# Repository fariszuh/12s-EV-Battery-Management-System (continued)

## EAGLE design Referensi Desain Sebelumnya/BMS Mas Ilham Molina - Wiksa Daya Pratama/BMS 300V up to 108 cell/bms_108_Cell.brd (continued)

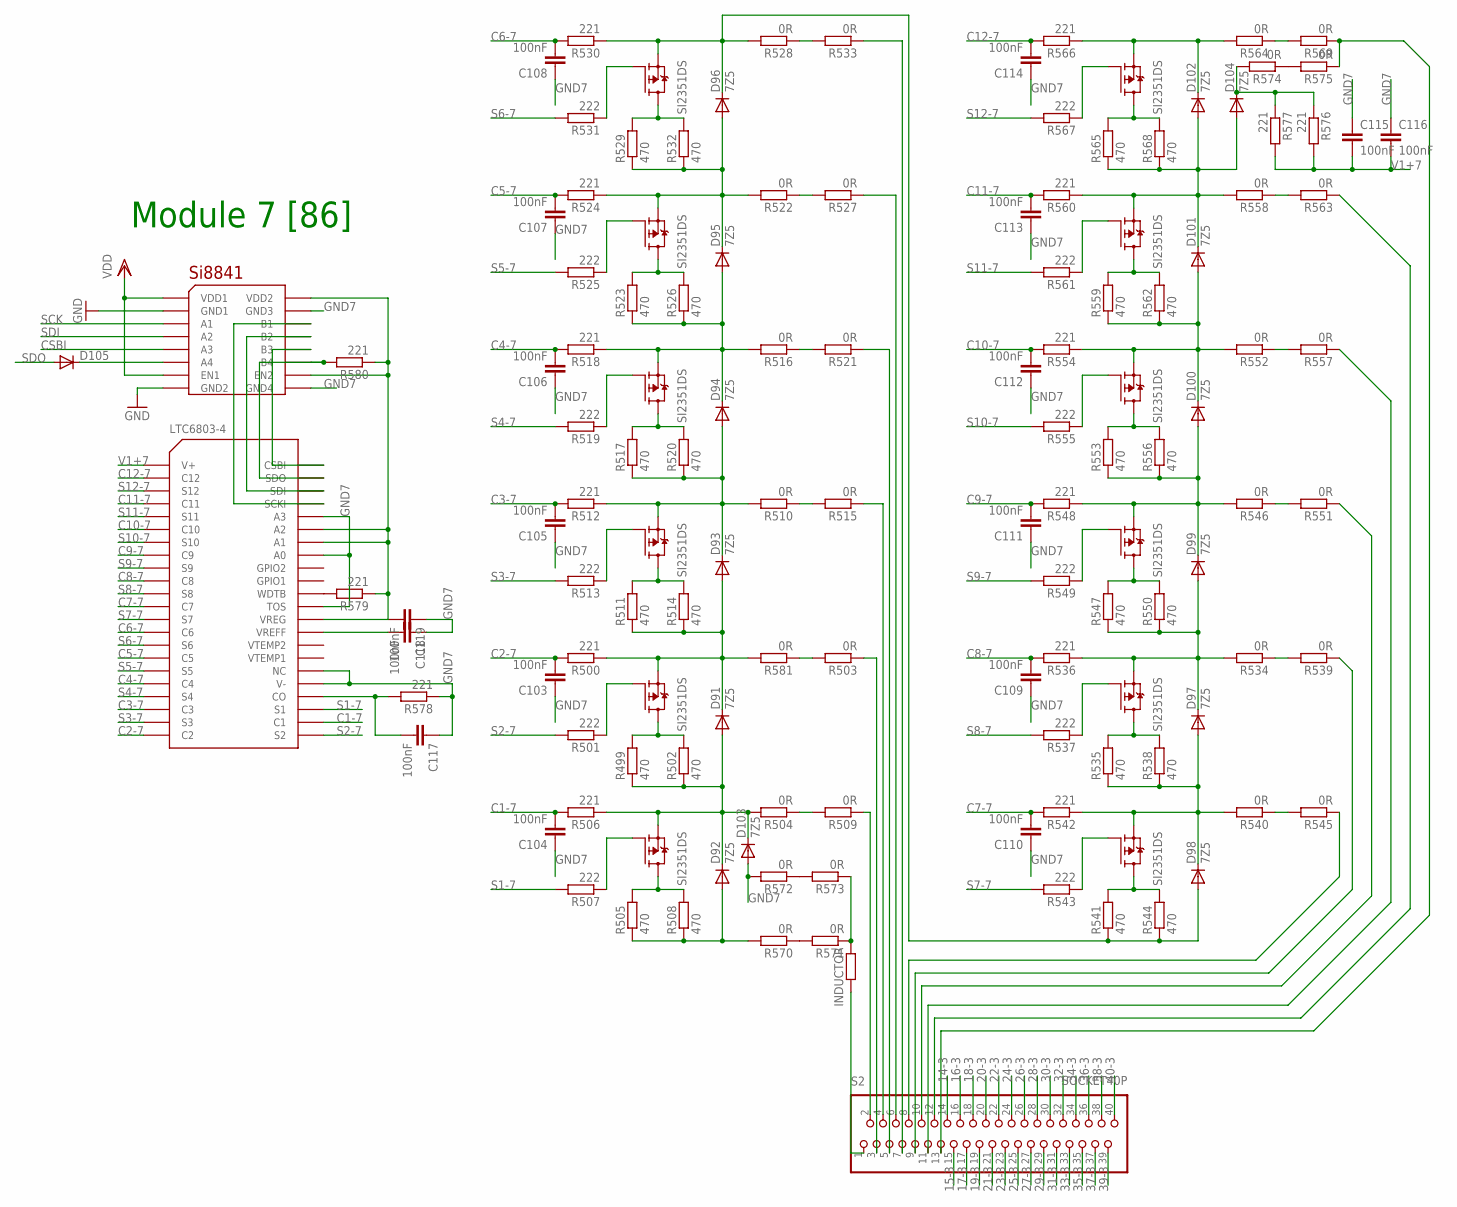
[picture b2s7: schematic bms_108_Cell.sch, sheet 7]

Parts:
C103, C104, C105, C106, C107, C108, C109, C110, C111, C112, C113, C114, C115, C116, C117, C118, C119: 100nF; C0805K
D91, D92, D93, D94, D95, D96, D97, D98, D99, D100, D101, D102, D103, D104: 7Z5; SMB
D105: DIODE-SOD123; SOD123
R499, R502, R505, R508, R511, R514, R517, R520, R523, R526, R529, R532, R535, R538, R541, R544, R547, R550, R553, R556, R559, R562, R565, R568: 470; R6332
R500, R506, R512, R518, R524, R530, R536, R542, R548, R554, R560, R566, R576, R577, R578, R579, R580: 221; R0805
R501, R507, R513, R519, R525, R531, R537, R543, R549, R555, R561, R567: 222; R0805
R503, R504, R509, R510, R515, R516, R521, R522, R527, R528, R533, R534, R539, R540, R545, R546, R551, R552, R557, R558, R563, R564, R569, R570, R571, R572, R573, R574, R575, R581: 0R; M1206
S2: SOCKET40P; 40PIN
U$91: LTC6803-4; SSOP44
U$92: SI8841; SO16
U$93, U$94, U$95, U$96, U$97, U$98, U$99, U$100, U$101, U$102, U$103, U$104: SI2351DS; SOT23
U$105: INDUCTOR; L2012C

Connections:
14-3: S2.14; also elsewhere on the board
15-3: S2.15; also elsewhere on the board
16-3: S2.16; also elsewhere on the board
17-3: S2.17; also elsewhere on the board
18-3: S2.18; also elsewhere on the board
19-3: S2.19; also elsewhere on the board
20-3: S2.20; also elsewhere on the board
21-3: S2.21; also elsewhere on the board
22-3: S2.22; also elsewhere on the board
23-3: S2.23; also elsewhere on the board
24-3: S2.24; also elsewhere on the board
25-3: S2.25; also elsewhere on the board
26-3: S2.26; also elsewhere on the board
27-3: S2.27
28-3: S2.28; also elsewhere on the board
29-3: S2.29; also elsewhere on the board
30-3: S2.30; also elsewhere on the board
31-3: S2.31; also elsewhere on the board
32-3: S2.32; also elsewhere on the board
33-3: S2.33; also elsewhere on the board
34-3: S2.34; also elsewhere on the board
35-3: S2.35; also elsewhere on the board
36-3: S2.36; also elsewhere on the board
37-3: S2.37; also elsewhere on the board
38-3: S2.38; also elsewhere on the board
39-3: S2.39; also elsewhere on the board
40-3: S2.40; also elsewhere on the board
C1-7: C104.2, R506.2, U$91.24 (C1)
C2-7: C103.2, R500.2, U$91.P$22 (C2)
C3-7: C105.2, R512.2, U$91.P$20 (C3)
C4-7: C106.2, R518.2, U$91.P$18 (C4)
C5-7: C107.2, R524.2, U$91.P$16 (C5)
C6-7: C108.2, R530.2, U$91.P$14 (C6)
C7-7: C110.2, R542.2, U$91.P$12 (C7)
C8-7: C109.2, R536.2, U$91.P$10 (C8)
C9-7: C111.2, R548.2, U$91.P$8 (C9)
C10-7: C112.2, R554.2, U$91.P$6 (C10)
C11-7: C113.2, R560.2, U$91.P$4 (C11)
C12-7: C114.2, R566.2, U$91.P$2 (C12)
CSBI: U$92.5 (A3); also elsewhere on the board
GND: U$92.2 (GND1), U$92.8 (GND2); also elsewhere on the board
GND7: C103.1, C104.1, C105.1, C106.1, C107.1, C108.1, C109.1, C110.1, C111.1, C112.1, C113.1, C114.1, C115.1, C116.1, C117.1, C118.1, C119.1, D103.A, R572.2, R578.1, U$91.27 (V-), U$91.28 (NC), U$91.33 (TOS), U$91.37 (A0), U$91.40 (A3), U$92.9 (GND4), U$92.15 (GND3)
unnamed: R501.1, U$93.1 (G)
unnamed: R499.2, R502.2, U$93.3 (D)
unnamed: D91.A, D92.C, D103.C, R499.1, R502.1, R504.2, R506.1, U$94.2 (S)
unnamed: R503.2, R581.1
unnamed: R507.1, U$94.1 (G)
unnamed: R505.2, R508.2, U$94.3 (D)
unnamed: R504.1, R509.2
unnamed: R513.1, U$95.1 (G)
unnamed: R511.2, R514.2, U$95.3 (D)
unnamed: D91.C, D93.A, R500.1, R511.1, R514.1, R581.2, U$93.2 (S)
unnamed: R510.1, R515.2
unnamed: R519.1, U$96.1 (G)
unnamed: R517.2, R520.2, U$96.3 (D)
unnamed: D93.C, D94.A, R510.2, R512.1, R517.1, R520.1, U$95.2 (S)
unnamed: R516.1, R521.2
unnamed: R525.1, U$97.1 (G)
unnamed: R523.2, R526.2, U$97.3 (D)
unnamed: D94.C, D95.A, R516.2, R518.1, R523.1, R526.1, U$96.2 (S)
unnamed: R522.1, R527.2
unnamed: R531.1, U$98.1 (G)
unnamed: R529.2, R532.2, U$98.3 (D)
unnamed: D95.C, D96.A, R522.2, R524.1, R529.1, R532.1, U$97.2 (S)
unnamed: R528.1, R533.2
unnamed: R537.1, U$99.1 (G)
unnamed: R535.2, R538.2, U$99.3 (D)
unnamed: D97.A, D98.C, R535.1, R538.1, R540.2, R542.1, U$100.2 (S)
unnamed: R534.1, R539.2
unnamed: R543.1, U$100.1 (G)
unnamed: R541.2, R544.2, U$100.3 (D)
unnamed: D96.C, D98.A, R528.2, R530.1, R541.1, R544.1, U$98.2 (S)
unnamed: R540.1, R545.2
unnamed: R549.1, U$101.1 (G)
unnamed: R547.2, R550.2, U$101.3 (D)
unnamed: D97.C, D99.A, R534.2, R536.1, R547.1, R550.1, U$99.2 (S)
unnamed: R546.1, R551.2
unnamed: R555.1, U$102.1 (G)
unnamed: R553.2, R556.2, U$102.3 (D)
unnamed: D99.C, D100.A, R546.2, R548.1, R553.1, R556.1, U$101.2 (S)
unnamed: R552.1, R557.2
unnamed: R561.1, U$103.1 (G)
unnamed: R559.2, R562.2, U$103.3 (D)
unnamed: D100.C, D101.A, R552.2, R554.1, R559.1, R562.1, U$102.2 (S)
unnamed: R558.1, R563.2
unnamed: D102.C, R564.2, R566.1, U$104.2 (S)
unnamed: R567.1, U$104.1 (G)
unnamed: R565.2, R568.2, U$104.3 (D)
unnamed: D101.C, D102.A, D104.A, R558.2, R560.1, R565.1, R568.1, U$103.2 (S)
unnamed: R564.1, R569.2
unnamed: R570.1, R571.2
unnamed: R571.1, R573.1, U$105.1
unnamed: D92.A, R505.1, R508.1, R570.2
unnamed: R572.1, R573.2
unnamed: R574.1, R575.2
unnamed: D104.C, R574.2, R576.1, R577.1
unnamed: R569.1, R575.1, S2.13
unnamed: C117.2, R578.2, U$91.26 (CO)
unnamed: C118.2, U$91.31 (VREFF)
unnamed: C119.2, R579.1, R580.1, U$91.32 (VREG), U$91.38 (A1), U$91.39 (A2), U$92.10 (EN2), U$92.16 (VDD2)
unnamed: R579.2, U$91.34 (WDTB)
unnamed: R580.2, U$91.43 (SDO), U$92.11 (B4)
unnamed: U$91.44 (CSBI), U$92.12 (B3)
unnamed: U$91.42 (SDI), U$92.13 (B2)
unnamed: U$91.41 (SCKI), U$92.14 (B1)
unnamed: S2.1, U$105.2
unnamed: R509.1, S2.2
unnamed: R503.1, S2.3
unnamed: R515.1, S2.4
unnamed: R521.1, S2.5
unnamed: R527.1, S2.6
unnamed: R533.1, S2.7
unnamed: R545.1, S2.8
unnamed: R539.1, S2.9
unnamed: R551.1, S2.10
unnamed: R557.1, S2.11
unnamed: R563.1, S2.12
unnamed: D105.C, U$92.6 (A4)
S1-7: R507.2, U$91.25 (S1)
S2-7: R501.2, U$91.23 (S2)
S3-7: R513.2, U$91.P$21 (S3)
S4-7: R519.2, U$91.P$19 (S4)
S5-7: R525.2, U$91.P$17 (S5)
S6-7: R531.2, U$91.P$15 (S6)
S7-7: R543.2, U$91.P$13 (S7)
S8-7: R537.2, U$91.P$11 (S8)
S9-7: R549.2, U$91.P$9 (S9)
S10-7: R555.2, U$91.P$7 (S10)
S11-7: R561.2, U$91.P$5 (S11)
S12-7: R567.2, U$91.P$3 (S12)
SCK: U$92.3 (A1); also elsewhere on the board
SDI: U$92.4 (A2); also elsewhere on the board
SDO: D105.A; also elsewhere on the board
V1+7: C115.2, C116.2, R576.2, R577.2, U$91.P$1 (V+)
VDD: U$92.1 (VDD1), U$92.7 (EN1); also elsewhere on the board

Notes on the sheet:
Module 7 [86]

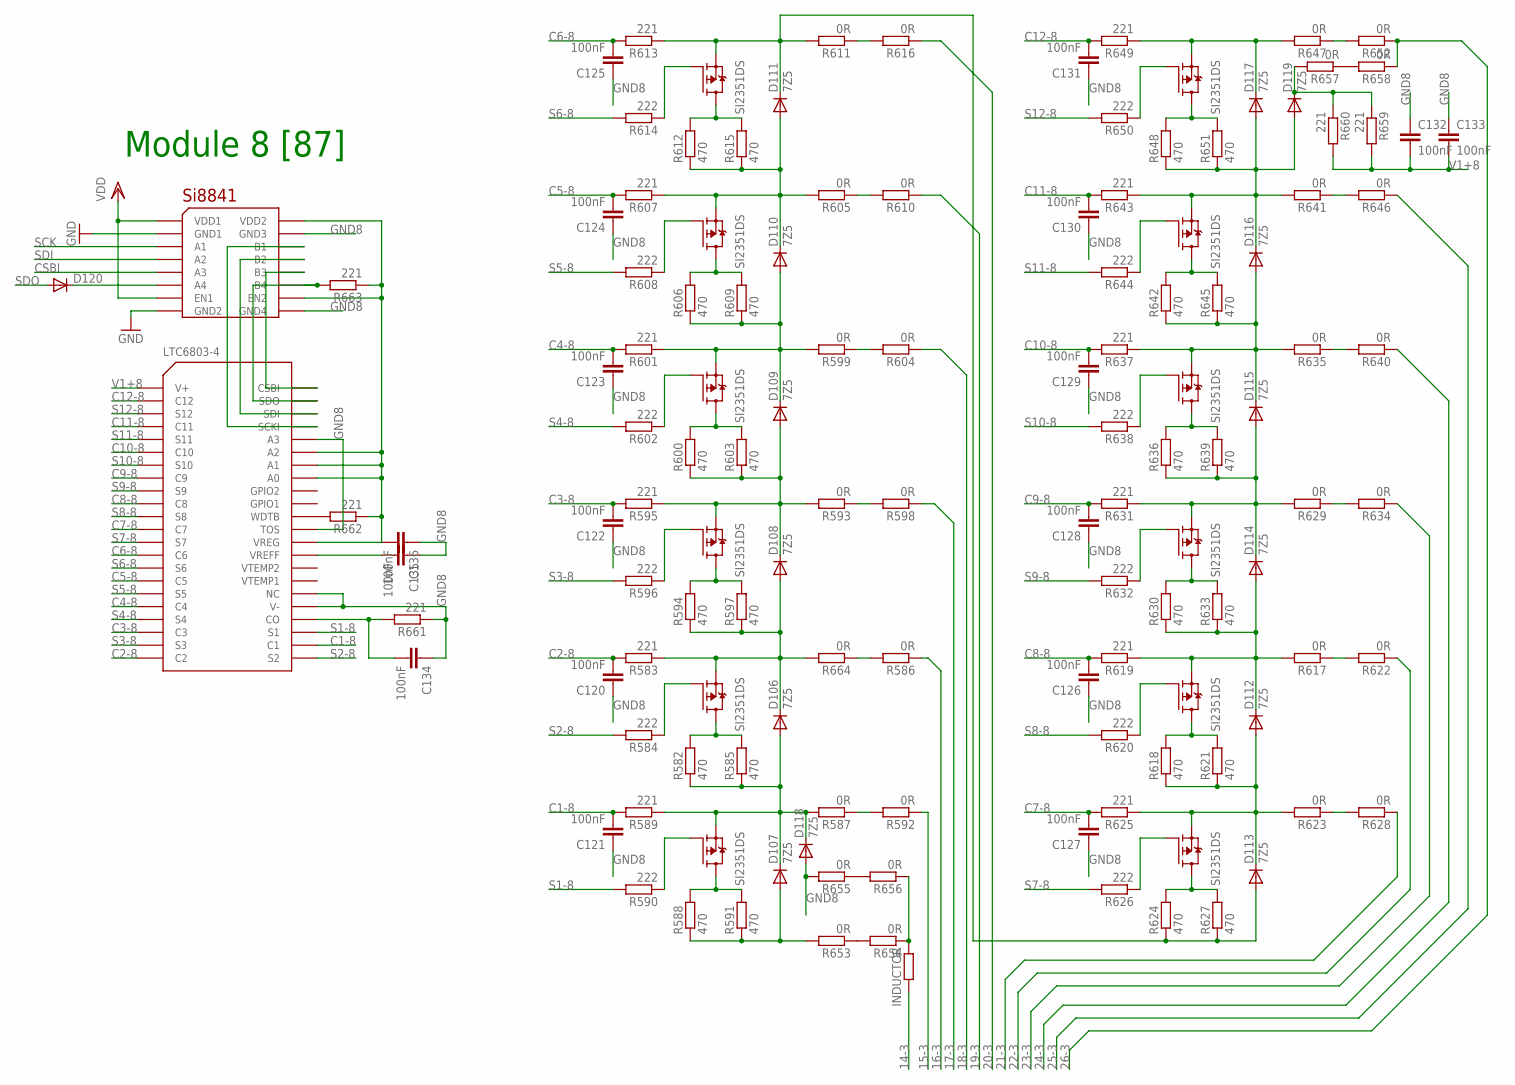
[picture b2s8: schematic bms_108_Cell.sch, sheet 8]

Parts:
C120, C121, C122, C123, C124, C125, C126, C127, C128, C129, C130, C131, C132, C133, C134, C135, C136: 100nF; C0805K
D106, D107, D108, D109, D110, D111, D112, D113, D114, D115, D116, D117, D118, D119: 7Z5; SMB
D120: DIODE-SOD123; SOD123
R582, R585, R588, R591, R594, R597, R600, R603, R606, R609, R612, R615, R618, R621, R624, R627, R630, R633, R636, R639, R642, R645, R648, R651: 470; R6332
R583, R589, R595, R601, R607, R613, R619, R625, R631, R637, R643, R649, R659, R660, R661, R662, R663: 221; R0805
R584, R590, R596, R602, R608, R614, R620, R626, R632, R638, R644, R650: 222; R0805
R586, R587, R592, R593, R598, R599, R604, R605, R610, R611, R616, R617, R622, R623, R628, R629, R634, R635, R640, R641, R646, R647, R652, R653, R654, R655, R656, R657, R658, R664: 0R; M1206
U$106: LTC6803-4; SSOP44
U$107: SI8841; SO16
U$108, U$109, U$110, U$111, U$112, U$113, U$114, U$115, U$116, U$117, U$118, U$119: SI2351DS; SOT23
U$120: INDUCTOR; L2012C

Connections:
14-3: U$120.2; also elsewhere on the board
15-3: R592.1; also elsewhere on the board
16-3: R586.1; also elsewhere on the board
17-3: R598.1; also elsewhere on the board
18-3: R604.1; also elsewhere on the board
19-3: R610.1; also elsewhere on the board
20-3: R616.1; also elsewhere on the board
21-3: R628.1; also elsewhere on the board
22-3: R622.1; also elsewhere on the board
23-3: R634.1; also elsewhere on the board
24-3: R640.1; also elsewhere on the board
25-3: R646.1; also elsewhere on the board
26-3: R652.1, R658.1; also elsewhere on the board
C1-8: C121.2, R589.2, U$106.24 (C1)
C2-8: C120.2, R583.2, U$106.P$22 (C2)
C3-8: C122.2, R595.2, U$106.P$20 (C3)
C4-8: C123.2, R601.2, U$106.P$18 (C4)
C5-8: C124.2, R607.2, U$106.P$16 (C5)
C6-8: C125.2, R613.2, U$106.P$14 (C6)
C7-8: C127.2, R625.2, U$106.P$12 (C7)
C8-8: C126.2, R619.2, U$106.P$10 (C8)
C9-8: C128.2, R631.2, U$106.P$8 (C9)
C10-8: C129.2, R637.2, U$106.P$6 (C10)
C11-8: C130.2, R643.2, U$106.P$4 (C11)
C12-8: C131.2, R649.2, U$106.P$2 (C12)
CSBI: U$107.5 (A3); also elsewhere on the board
GND: U$107.2 (GND1), U$107.8 (GND2); also elsewhere on the board
GND8: C120.1, C121.1, C122.1, C123.1, C124.1, C125.1, C126.1, C127.1, C128.1, C129.1, C130.1, C131.1, C132.1, C133.1, C134.1, C135.1, C136.1, D118.A, R655.2, R661.1, U$106.27 (V-), U$106.28 (NC), U$106.33 (TOS), U$106.40 (A3), U$107.9 (GND4), U$107.15 (GND3)
unnamed: R584.1, U$108.1 (G)
unnamed: R582.2, R585.2, U$108.3 (D)
unnamed: D106.A, D107.C, D118.C, R582.1, R585.1, R587.2, R589.1, U$109.2 (S)
unnamed: R586.2, R664.1
unnamed: R590.1, U$109.1 (G)
unnamed: R588.2, R591.2, U$109.3 (D)
unnamed: R587.1, R592.2
unnamed: R596.1, U$110.1 (G)
unnamed: R594.2, R597.2, U$110.3 (D)
unnamed: D106.C, D108.A, R583.1, R594.1, R597.1, R664.2, U$108.2 (S)
unnamed: R593.1, R598.2
unnamed: R602.1, U$111.1 (G)
unnamed: R600.2, R603.2, U$111.3 (D)
unnamed: D108.C, D109.A, R593.2, R595.1, R600.1, R603.1, U$110.2 (S)
unnamed: R599.1, R604.2
unnamed: R608.1, U$112.1 (G)
unnamed: R606.2, R609.2, U$112.3 (D)
unnamed: D109.C, D110.A, R599.2, R601.1, R606.1, R609.1, U$111.2 (S)
unnamed: R605.1, R610.2
unnamed: R614.1, U$113.1 (G)
unnamed: R612.2, R615.2, U$113.3 (D)
unnamed: D110.C, D111.A, R605.2, R607.1, R612.1, R615.1, U$112.2 (S)
unnamed: R611.1, R616.2
unnamed: R620.1, U$114.1 (G)
unnamed: R618.2, R621.2, U$114.3 (D)
unnamed: D112.A, D113.C, R618.1, R621.1, R623.2, R625.1, U$115.2 (S)
unnamed: R617.1, R622.2
unnamed: R626.1, U$115.1 (G)
unnamed: R624.2, R627.2, U$115.3 (D)
unnamed: D111.C, D113.A, R611.2, R613.1, R624.1, R627.1, U$113.2 (S)
unnamed: R623.1, R628.2
unnamed: R632.1, U$116.1 (G)
unnamed: R630.2, R633.2, U$116.3 (D)
unnamed: D112.C, D114.A, R617.2, R619.1, R630.1, R633.1, U$114.2 (S)
unnamed: R629.1, R634.2
unnamed: R638.1, U$117.1 (G)
unnamed: R636.2, R639.2, U$117.3 (D)
unnamed: D114.C, D115.A, R629.2, R631.1, R636.1, R639.1, U$116.2 (S)
unnamed: R635.1, R640.2
unnamed: R644.1, U$118.1 (G)
unnamed: R642.2, R645.2, U$118.3 (D)
unnamed: D115.C, D116.A, R635.2, R637.1, R642.1, R645.1, U$117.2 (S)
unnamed: R641.1, R646.2
unnamed: D117.C, R647.2, R649.1, U$119.2 (S)
unnamed: R650.1, U$119.1 (G)
unnamed: R648.2, R651.2, U$119.3 (D)
unnamed: D116.C, D117.A, D119.A, R641.2, R643.1, R648.1, R651.1, U$118.2 (S)
unnamed: R647.1, R652.2
unnamed: R653.1, R654.2
unnamed: R654.1, R656.1, U$120.1
unnamed: D107.A, R588.1, R591.1, R653.2
unnamed: R655.1, R656.2
unnamed: R657.1, R658.2
unnamed: D119.C, R657.2, R659.1, R660.1
unnamed: C134.2, R661.2, U$106.26 (CO)
unnamed: C135.2, U$106.31 (VREFF)
unnamed: C136.2, R662.1, R663.1, U$106.32 (VREG), U$106.37 (A0), U$106.38 (A1), U$106.39 (A2), U$107.10 (EN2), U$107.16 (VDD2)
unnamed: R662.2, U$106.34 (WDTB)
unnamed: R663.2, U$106.43 (SDO), U$107.11 (B4)
unnamed: U$106.44 (CSBI), U$107.12 (B3)
unnamed: U$106.42 (SDI), U$107.13 (B2)
unnamed: U$106.41 (SCKI), U$107.14 (B1)
unnamed: D120.C, U$107.6 (A4)
S1-8: R590.2, U$106.25 (S1)
S2-8: R584.2, U$106.23 (S2)
S3-8: R596.2, U$106.P$21 (S3)
S4-8: R602.2, U$106.P$19 (S4)
S5-8: R608.2, U$106.P$17 (S5)
S6-8: R614.2, U$106.P$15 (S6)
S7-8: R626.2, U$106.P$13 (S7)
S8-8: R620.2, U$106.P$11 (S8)
S9-8: R632.2, U$106.P$9 (S9)
S10-8: R638.2, U$106.P$7 (S10)
S11-8: R644.2, U$106.P$5 (S11)
S12-8: R650.2, U$106.P$3 (S12)
SCK: U$107.3 (A1); also elsewhere on the board
SDI: U$107.4 (A2); also elsewhere on the board
SDO: D120.A; also elsewhere on the board
V1+8: C132.2, C133.2, R659.2, R660.2, U$106.P$1 (V+)
VDD: U$107.1 (VDD1), U$107.7 (EN1); also elsewhere on the board

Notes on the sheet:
Module 8 [87]

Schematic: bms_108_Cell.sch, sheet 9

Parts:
C137, C138, C139, C140, C141, C142, C143, C144, C145, C146, C147, C148, C149, C150, C151, C152, C153: 100nF; C0805K
D121, D122, D123, D124, D125, D126, D127, D128, D129, D130, D131, D132, D133, D134: 7Z5; SMB
D135: DIODE-SOD123; SOD123
R665, R668, R671, R674, R677, R680, R683, R686, R689, R692, R695, R698, R701, R704, R707, R710, R713, R716, R719, R722, R725, R728, R731, R734: 470; R6332
R666, R672, R678, R684, R690, R696, R702, R708, R714, R720, R726, R732, R742, R743, R744, R745, R746: 221; R0805
R667, R673, R679, R685, R691, R697, R703, R709, R715, R721, R727, R733: 222; R0805
R669, R670, R675, R676, R681, R682, R687, R688, R693, R694, R699, R700, R705, R706, R711, R712, R717, R718, R723, R724, R729, R730, R735, R736, R737, R738, R739, R740, R741, R747: 0R; M1206
U$121: LTC6803-4; SSOP44
U$122: SI8841; SO16
U$123, U$124, U$125, U$126, U$127, U$128, U$129, U$130, U$131, U$132, U$133, U$134: SI2351DS; SOT23
U$135: INDUCTOR; L2012C

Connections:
28-3: U$135.2; also elsewhere on the board
29-3: R675.1; also elsewhere on the board
30-3: R669.1; also elsewhere on the board
31-3: R681.1; also elsewhere on the board
32-3: R687.1; also elsewhere on the board
33-3: R693.1; also elsewhere on the board
34-3: R699.1; also elsewhere on the board
35-3: R711.1; also elsewhere on the board
36-3: R705.1; also elsewhere on the board
37-3: R717.1; also elsewhere on the board
38-3: R723.1; also elsewhere on the board
39-3: R729.1; also elsewhere on the board
40-3: R735.1, R741.1; also elsewhere on the board
C1-9: C138.2, R672.2, U$121.24 (C1)
C2-9: C137.2, R666.2, U$121.P$22 (C2)
C3-9: C139.2, R678.2, U$121.P$20 (C3)
C4-9: C140.2, R684.2, U$121.P$18 (C4)
C5-9: C141.2, R690.2, U$121.P$16 (C5)
C6-9: C142.2, R696.2, U$121.P$14 (C6)
C7-9: C144.2, R708.2, U$121.P$12 (C7)
C8-9: C143.2, R702.2, U$121.P$10 (C8)
C9-9: C145.2, R714.2, U$121.P$8 (C9)
C10-9: C146.2, R720.2, U$121.P$6 (C10)
C11-9: C147.2, R726.2, U$121.P$4 (C11)
C12-9: C148.2, R732.2, U$121.P$2 (C12)
CSBI: U$122.5 (A3); also elsewhere on the board
GND: U$122.2 (GND1), U$122.8 (GND2); also elsewhere on the board
GND9: C137.1, C138.1, C139.1, C140.1, C141.1, C142.1, C143.1, C144.1, C145.1, C146.1, C147.1, C148.1, C149.1, C150.1, C151.1, C152.1, C153.1, D133.A, R738.2, R744.1, U$121.27 (V-), U$121.28 (NC), U$121.33 (TOS), U$121.37 (A0), U$121.38 (A1), U$121.39 (A2), U$122.9 (GND4), U$122.15 (GND3)
unnamed: R667.1, U$123.1 (G)
unnamed: R665.2, R668.2, U$123.3 (D)
unnamed: D121.A, D122.C, D133.C, R665.1, R668.1, R670.2, R672.1, U$124.2 (S)
unnamed: R669.2, R747.1
unnamed: R673.1, U$124.1 (G)
unnamed: R671.2, R674.2, U$124.3 (D)
unnamed: R670.1, R675.2
unnamed: R679.1, U$125.1 (G)
unnamed: R677.2, R680.2, U$125.3 (D)
unnamed: D121.C, D123.A, R666.1, R677.1, R680.1, R747.2, U$123.2 (S)
unnamed: R676.1, R681.2
unnamed: R685.1, U$126.1 (G)
unnamed: R683.2, R686.2, U$126.3 (D)
unnamed: D123.C, D124.A, R676.2, R678.1, R683.1, R686.1, U$125.2 (S)
unnamed: R682.1, R687.2
unnamed: R691.1, U$127.1 (G)
unnamed: R689.2, R692.2, U$127.3 (D)
unnamed: D124.C, D125.A, R682.2, R684.1, R689.1, R692.1, U$126.2 (S)
unnamed: R688.1, R693.2
unnamed: R697.1, U$128.1 (G)
unnamed: R695.2, R698.2, U$128.3 (D)
unnamed: D125.C, D126.A, R688.2, R690.1, R695.1, R698.1, U$127.2 (S)
unnamed: R694.1, R699.2
unnamed: R703.1, U$129.1 (G)
unnamed: R701.2, R704.2, U$129.3 (D)
unnamed: D127.A, D128.C, R701.1, R704.1, R706.2, R708.1, U$130.2 (S)
unnamed: R700.1, R705.2
unnamed: R709.1, U$130.1 (G)
unnamed: R707.2, R710.2, U$130.3 (D)
unnamed: D126.C, D128.A, R694.2, R696.1, R707.1, R710.1, U$128.2 (S)
unnamed: R706.1, R711.2
unnamed: R715.1, U$131.1 (G)
unnamed: R713.2, R716.2, U$131.3 (D)
unnamed: D127.C, D129.A, R700.2, R702.1, R713.1, R716.1, U$129.2 (S)
unnamed: R712.1, R717.2
unnamed: R721.1, U$132.1 (G)
unnamed: R719.2, R722.2, U$132.3 (D)
unnamed: D129.C, D130.A, R712.2, R714.1, R719.1, R722.1, U$131.2 (S)
unnamed: R718.1, R723.2
unnamed: R727.1, U$133.1 (G)
unnamed: R725.2, R728.2, U$133.3 (D)
unnamed: D130.C, D131.A, R718.2, R720.1, R725.1, R728.1, U$132.2 (S)
unnamed: R724.1, R729.2
unnamed: D132.C, R730.2, R732.1, U$134.2 (S)
unnamed: R733.1, U$134.1 (G)
unnamed: R731.2, R734.2, U$134.3 (D)
unnamed: D131.C, D132.A, D134.A, R724.2, R726.1, R731.1, R734.1, U$133.2 (S)
unnamed: R730.1, R735.2
unnamed: R736.1, R737.2
unnamed: R737.1, R739.1, U$135.1
unnamed: D122.A, R671.1, R674.1, R736.2
unnamed: R738.1, R739.2
unnamed: R740.1, R741.2
unnamed: D134.C, R740.2, R742.1, R743.1
unnamed: C151.2, R744.2, U$121.26 (CO)
unnamed: C152.2, U$121.31 (VREFF)
unnamed: C153.2, R745.1, R746.1, U$121.32 (VREG), U$121.40 (A3), U$122.10 (EN2), U$122.16 (VDD2)
unnamed: R745.2, U$121.34 (WDTB)
unnamed: R746.2, U$121.43 (SDO), U$122.11 (B4)
unnamed: U$121.44 (CSBI), U$122.12 (B3)
unnamed: U$121.42 (SDI), U$122.13 (B2)
unnamed: U$121.41 (SCKI), U$122.14 (B1)
unnamed: D135.C, U$122.6 (A4)
S1-9: R673.2, U$121.25 (S1)
S2-9: R667.2, U$121.23 (S2)
S3-9: R679.2, U$121.P$21 (S3)
S4-9: R685.2, U$121.P$19 (S4)
S5-9: R691.2, U$121.P$17 (S5)
S6-9: R697.2, U$121.P$15 (S6)
S7-9: R709.2, U$121.P$13 (S7)
S8-9: R703.2, U$121.P$11 (S8)
S9-9: R715.2, U$121.P$9 (S9)
S10-9: R721.2, U$121.P$7 (S10)
S11-9: R727.2, U$121.P$5 (S11)
S12-9: R733.2, U$121.P$3 (S12)
SCK: U$122.3 (A1); also elsewhere on the board
SDI: U$122.4 (A2); also elsewhere on the board
SDO: D135.A; also elsewhere on the board
V1+9: C149.2, C150.2, R742.2, R743.2, U$121.P$1 (V+)
VDD: U$122.1 (VDD1), U$122.7 (EN1); also elsewhere on the board

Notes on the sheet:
Module 9 [88]

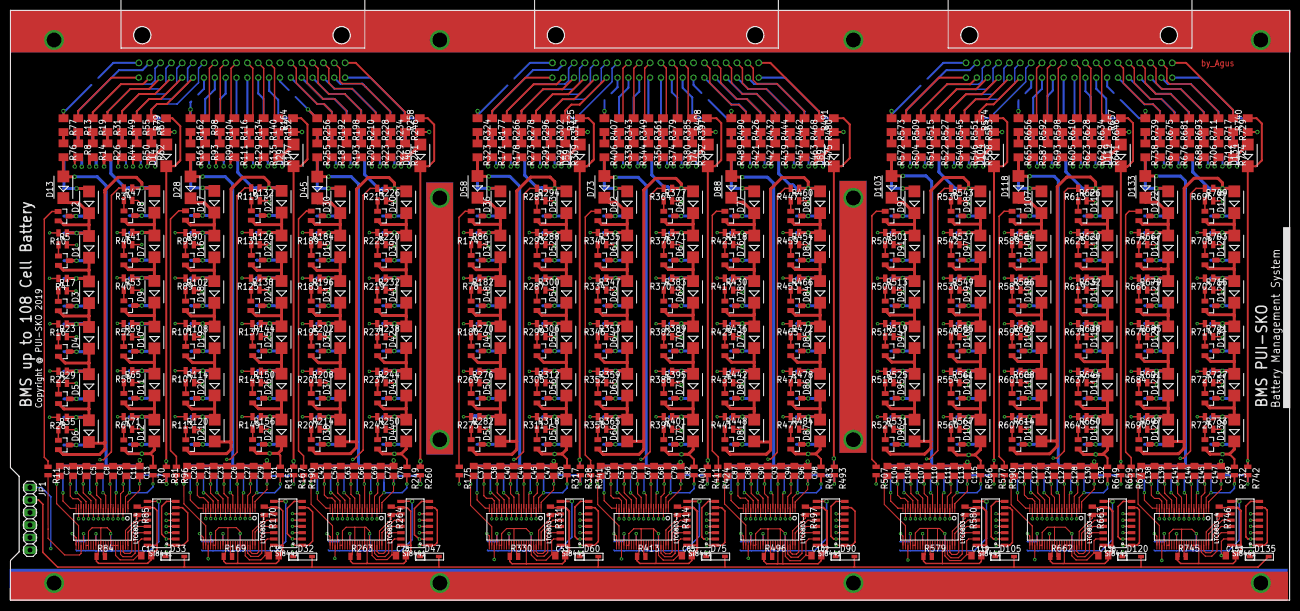
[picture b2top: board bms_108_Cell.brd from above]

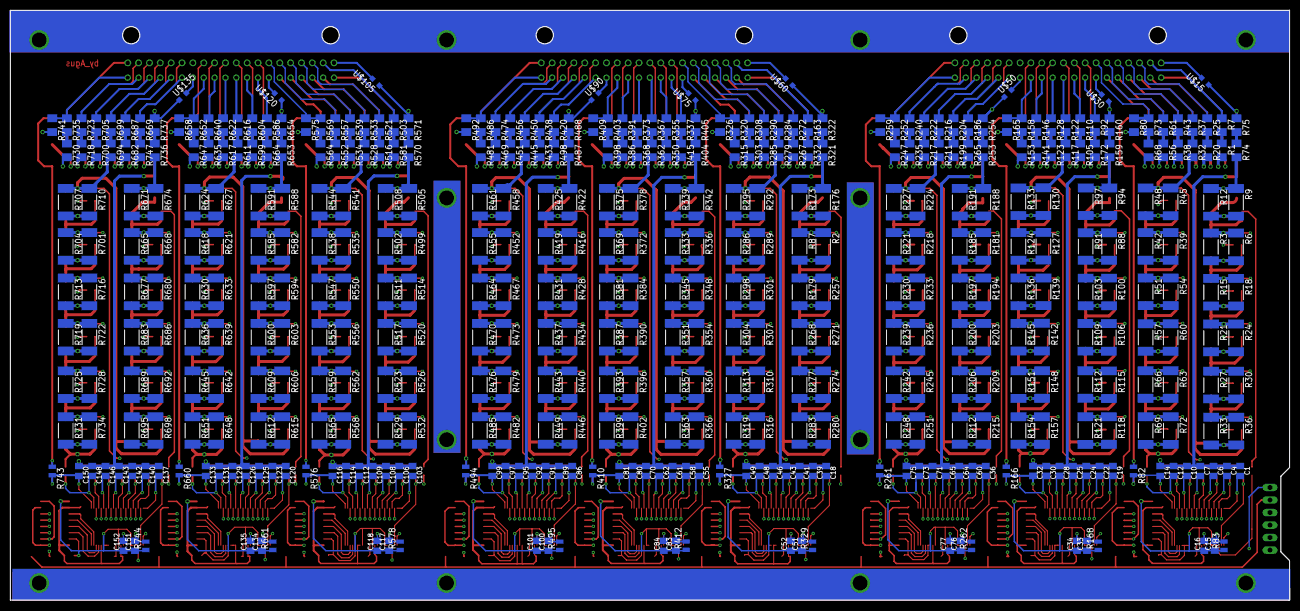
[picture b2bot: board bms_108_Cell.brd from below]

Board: 2 copper layers, 259.2 x 119.5 mm, 1174 parts (459 on the bottom side), 924 nets.
